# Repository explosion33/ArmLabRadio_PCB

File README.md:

# ArmLabRadio_PCB
KiCad files for CC1200 and STM32 based 2m / 70cm radio

## Software
This is the hardware repo for the project, checkout

[CC1200stm32](https://github.com/explosion33/CC1200stm32) for the embedded device code

[ArmLabCC1200](https://github.com/explosion33/ArmLabCC1200) for Serial / I2C inteface libraries

## Other
checkout

[RGRadioAPI](https://github.com/explosion33/RGRadioApi) for an example use case

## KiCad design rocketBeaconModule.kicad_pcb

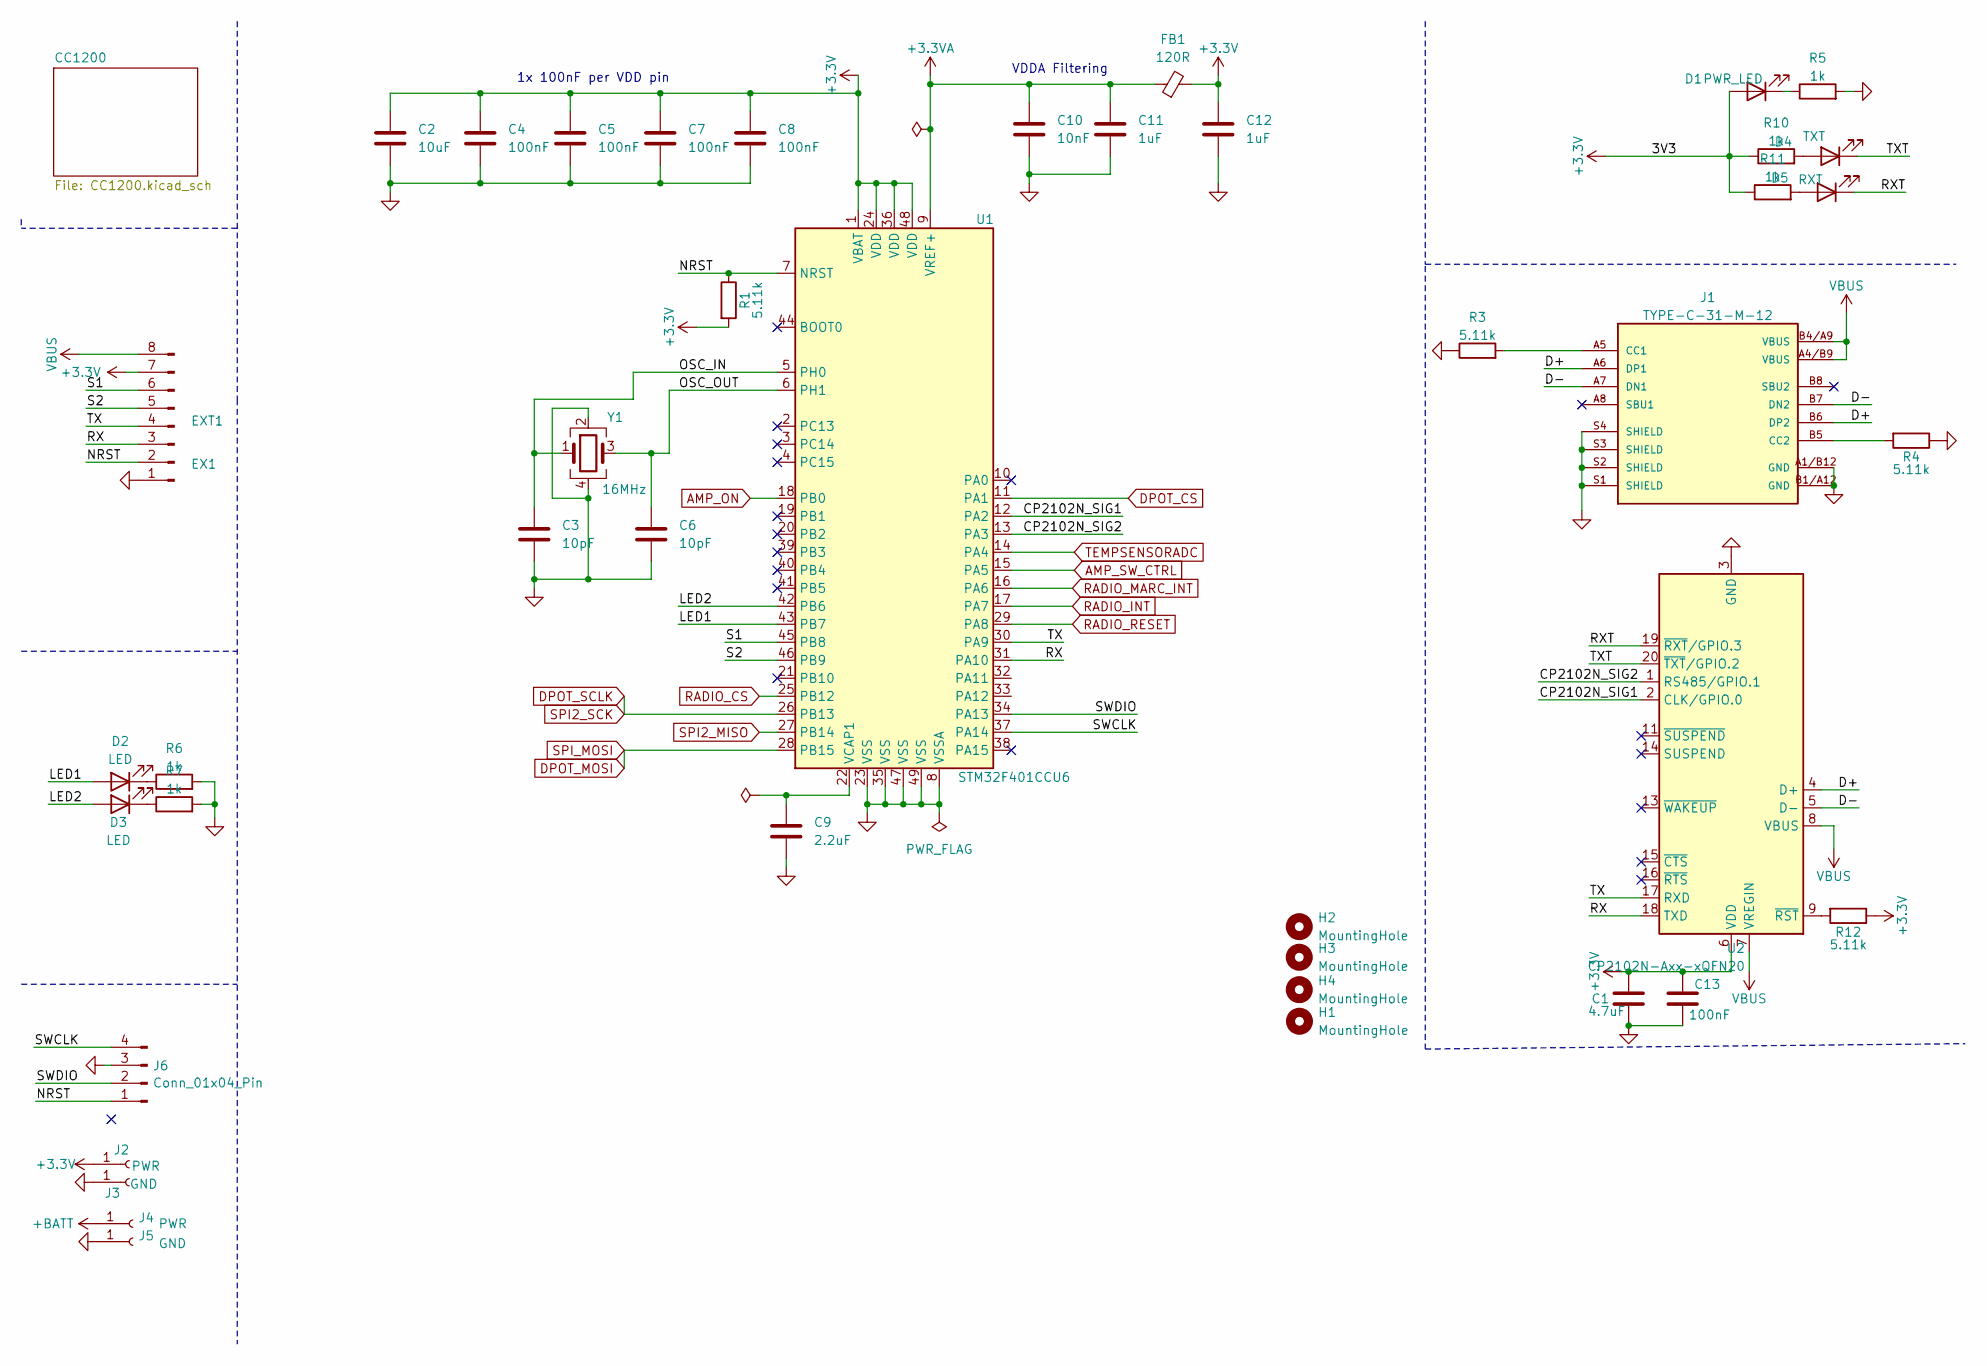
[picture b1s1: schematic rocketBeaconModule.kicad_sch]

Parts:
C1: 4.7uF; C_0603_1608Metric; LCSC Part C71631
C2: 10uF; C_0603_1608Metric; LCSC Part C19702
C3, C6: 10pF; C_0402_1005Metric; LCSC Part C32949
C4, C5, C7, C8, C13: 100nF; C_0402_1005Metric; LCSC Part C307331
C9: 2.2uF; C_0402_1005Metric; LCSC Part C12530
C10: 10nF; C_0402_1005Metric; LCSC Part C15195
C11, C12: 1uF; C_0402_1005Metric; LCSC Part C52923
D1: PWR_LED; LED_0402_1005Metric; LCSC Part C5160717
D2: LED; LED_0402_1005Metric; LCSC Part C131223
D3: LED; LED_0402_1005Metric; LCSC Part C130722
D4: TXT; LED_0402_1005Metric; LCSC Part C136765
D5: RXT; LED_0402_1005Metric; LCSC Part C130722
EX1: EXT1; Molex_200528-0080_1x08-1MP_P1.00mm_Horizontal; LCSC Part C132510
FB1: 120R; L_0603_1608Metric; LCSC Part C85831
H1, H2, H3, H4: MountingHole; MountingHole_2.2mm_M2
J1: TYPE-C-31-M-12; HRO_TYPE-C-31-M-12; PARTREV 2020.12.08; LCSC Part C165948
J2, J4: PWR; TestPoint_THTPad_4.0x4.0mm_Drill2.0mm
J3, J5: GND; TestPoint_THTPad_4.0x4.0mm_Drill2.0mm
J6: Conn_01x04_Pin; PinHeader_1x04_P2.54mm_Vertical
R1, R3, R4, R12: 5.11k; R_0402_1005Metric; LCSC Part C25906
R5, R6, R7, R10, R11: 1k; R_0402_1005Metric; LCSC Part C11702
U1: STM32F401CCU6; QFN-48-1EP_7x7mm_P0.5mm_EP5.6x5.6mm; LCSC Part C79861
U2: CP2102N-Axx-xQFN20; WFQFN-20; LCSC Part C969913
Y1: 16MHz; Crystal_SMD_3225-4Pin_3.2x2.5mm; LCSC Part C13738

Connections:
+3.3V: C1.1, C2.1, C4.1, C5.1, C7.1, C8.1, C12.1, C13.1, D1.2 (A), EX1.7, FB1.2, J2.1, R1.2, R10.1, R11.1, R12.1, U1.1 (VBAT), U1.24 (VDD), U1.36 (VDD), U1.48 (VDD), U2.6 (VDD); also elsewhere on the board
+3.3VA: C10.1, C11.1, FB1.1, U1.9 (VREF+)
+BATT: J4.1; also elsewhere on the board
/CP2102N_SIG1: U1.12 (PA2), U2.2 (CLK/GPIO.0)
/CP2102N_SIG2: U1.13 (PA3), U2.1 (RS485/GPIO.1)
/D+: J1.A6 (DP1), J1.B6 (DP2), U2.4 (D+)
/D-: J1.A7 (DN1), J1.B7 (DN2), U2.5 (D-)
/LED1: D2.2 (A), U1.43 (PB7)
/LED2: D3.2 (A), U1.42 (PB6)
/NRST: EX1.2, J6.1, R1.1, U1.7 (NRST)
/OSC_IN: C3.1, U1.5 (PH0), Y1.1
/OSC_OUT: C6.1, U1.6 (PH1), Y1.3
/RX: EX1.3, U1.31 (PA10), U2.18 (TXD)
/RXT: D5.1 (K), U2.19 (~RXT/GPIO.3)
/S1: EX1.6, U1.45 (PB8)
/S2: EX1.5, U1.46 (PB9)
/SWCLK: J6.4, U1.37 (PA14)
/SWDIO: J6.2, U1.34 (PA13)
/TX: EX1.4, U1.30 (PA9), U2.17 (RXD)
/TXT: D4.1 (K), U2.20 (~TXT/GPIO.2)
AMP_ON: U1.18 (PB0); also elsewhere on the board
AMP_SW_CTRL: U1.15 (PA5); also elsewhere on the board
DPOT_CS: U1.11 (PA1); also elsewhere on the board
DPOT_MOSI: U1.28 (PB15); also elsewhere on the board
DPOT_SCLK: U1.26 (PB13); also elsewhere on the board
GND: C1.2, C2.2, C3.2, C4.2, C5.2, C6.2, C7.2, C8.2, C9.2, C10.2, C11.2, C12.2, C13.2, EX1.1, J1.A1/B12 (GND), J1.B1/A12 (GND), J1.S1 (SHIELD), J1.S2 (SHIELD), J1.S3 (SHIELD), J1.S4 (SHIELD), J3.1, J5.1, J6.3, R3.1, R4.1, R5.2, R6.2, R7.2, U1.8 (VSSA), U1.23 (VSS), U1.35 (VSS), U1.47 (VSS), U1.49 (VSS), U2.3 (GND), U2.12 (GND), Y1.2, Y1.4; also elsewhere on the board
unnamed: D1.1 (K), R5.1
unnamed: D2.1 (K), R6.1
unnamed: D3.1 (K), R7.1
unnamed: D4.2 (A), R10.2
unnamed: D5.2 (A), R11.2
unnamed: J1.A5 (CC1), R3.2
unnamed: J1.B5 (CC2), R4.2
unnamed: C9.1, U1.22 (VCAP1)
unnamed: R12.2, U2.9 (~RST)
RADIO_CS: U1.25 (PB12); also elsewhere on the board
RADIO_INT: U1.17 (PA7); also elsewhere on the board
RADIO_MARC_INT: U1.16 (PA6); also elsewhere on the board
RADIO_RESET: U1.29 (PA8); also elsewhere on the board
SPI2_MISO: U1.27 (PB14); also elsewhere on the board
TEMPSENSORADC: U1.14 (PA4); also elsewhere on the board
VBUS: EX1.8, J1.A4/B9 (VBUS), J1.B4/A9 (VBUS), U2.7 (VREGIN), U2.8 (VBUS)

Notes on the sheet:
VDDA Filtering
1x 100nF per VDD pin

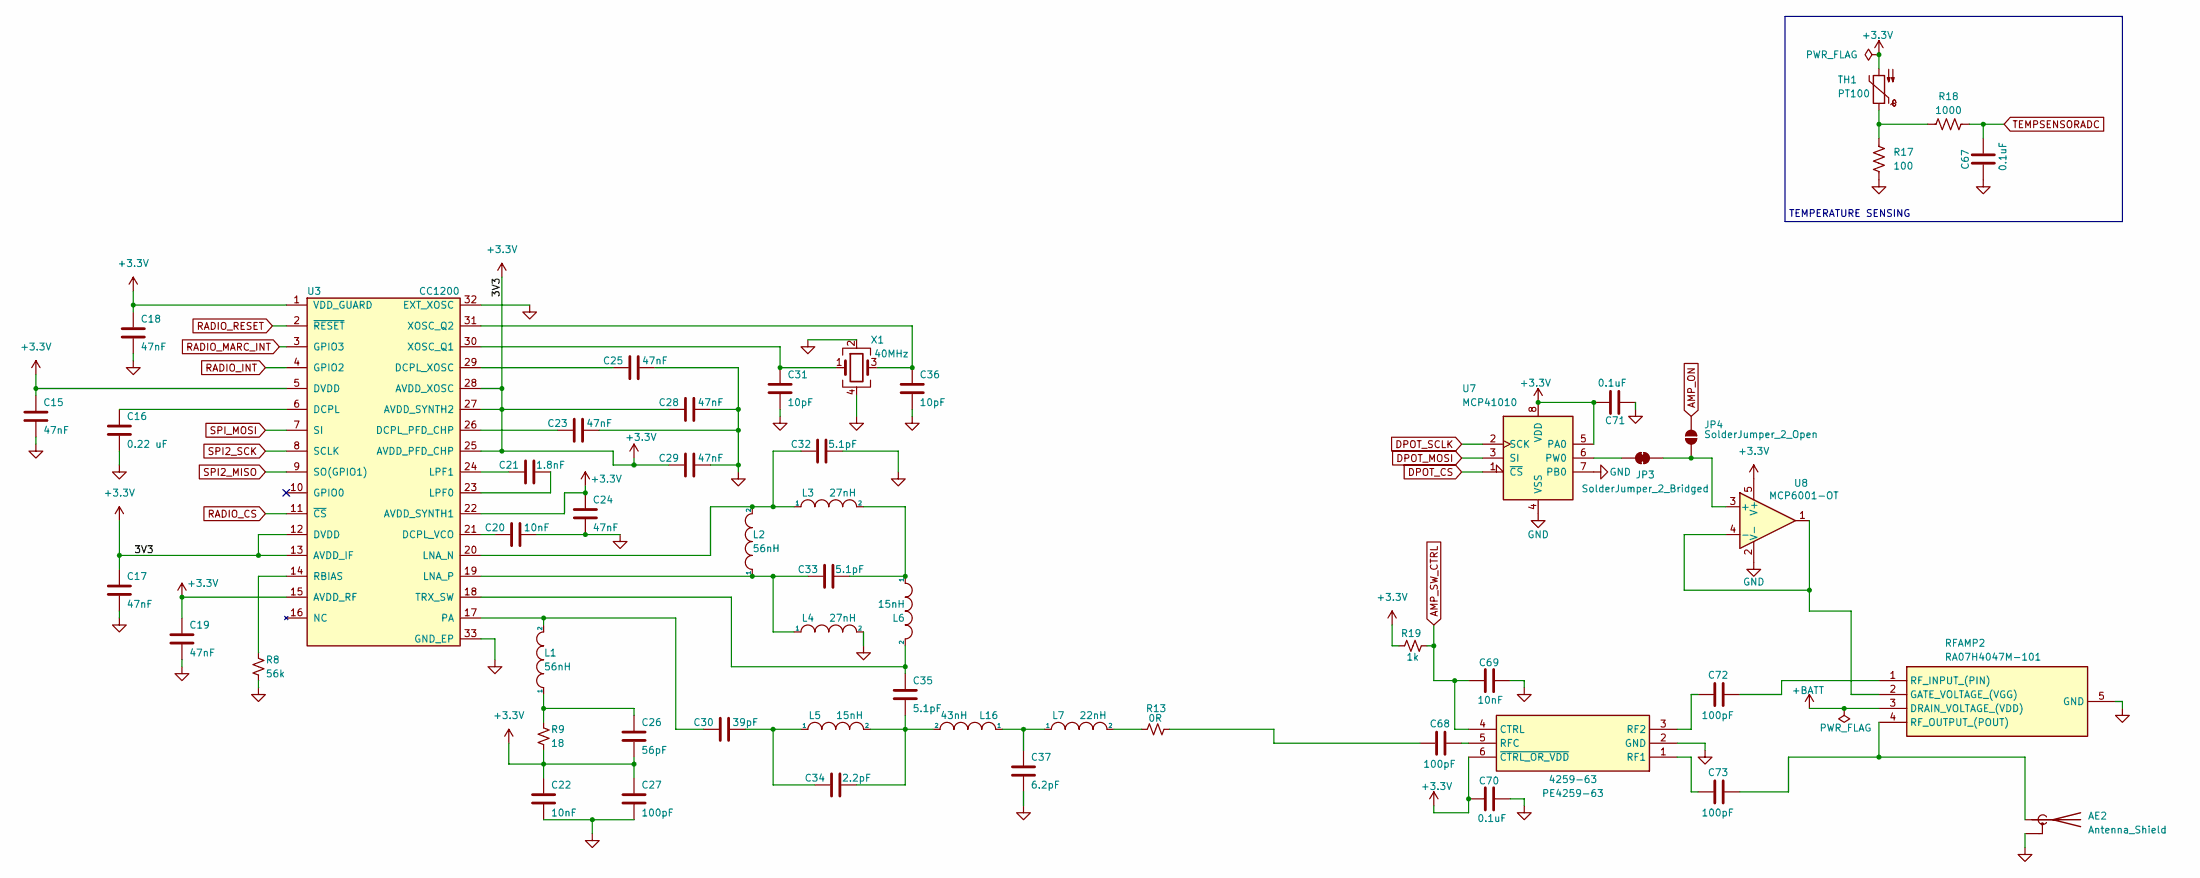
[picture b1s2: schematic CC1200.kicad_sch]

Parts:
AE2: Antenna_Shield; SMA_Amphenol_132134-11_Vertical; LCSC Part C496549
C15, C17, C18, C19, C23, C24, C25, C28, C29: 47nF; C_0402_1005Metric; LCSC Part C508865
C16: 0.22 uF; C_0402_1005Metric; LCSC Part C16772
C20, C22: 10nF; C_0402_1005Metric; LCSC Part C15195
C21: 1.8nF; C_0402_1005Metric; LCSC Part C162192
C26: 56pF; C_0402_1005Metric; LCSC Part C335543
C27: 100pF; C_0402_1005Metric; LCSC Part C126492
C30: 39pF; C_0402_1005Metric; LCSC Part C86288
C31, C36: 10pF; C_0402_1005Metric; LCSC Part C32949
C32, C33, C35: 5.1pF; C_0402_1005Metric; LCSC Part C281761
C34: 2.2pF; C_0402_1005Metric; LCSC Part C159806
C37: 6.2pF; C_0402_1005Metric; LCSC Part C325456
C67, C71: 0.1uF; C_0402_1005Metric; LCSC Part C1525
C68, C72, C73: 100pF; C_0402_1005Metric; LCSC C1546
C69: 10nF; C_0402_1005Metric; LCSC C15195
C70: 0.1uF; C_0402_1005Metric; LCSC C1525
JP3: SolderJumper_2_Bridged; SolderJumper-2_P1.3mm_Bridged_RoundedPad1.0x1.5mm
JP4: SolderJumper_2_Open; SolderJumper-2_P1.3mm_Open_RoundedPad1.0x1.5mm
L1, L2: 56nH; C_0402_1005Metric; LCSC Part C167484
L3, L4: 27nH; C_0402_1005Metric; LCSC Part C12669
L5, L6: 15nH; C_0402_1005Metric; LCSC Part C27143
L7: 22nH; C_0402_1005Metric; LCSC Part C12670
L16: 43nH; L_0402_1005Metric; LCSC Part C167478
PE4259-63: 4259-63; SOT-363_SC-70-6; Manufacturer_Part_Number 4259-63; LCSC Part C470892
R8: 56k; C_0402_1005Metric; LCSC Part C25796
R9: 18; R_0402_1005Metric; LCSC Part C25084
R13: 0R; C_0402_1005Metric; LCSC Part C138289
R17: 100; R_0402_1005Metric; LCSC Part C25076
R18: 1000; R_0402_1005Metric; LCSC Part C21190
R19: 1k; R_0402_1005Metric; LCSC C11702
RFAMP2: RA07H4047M-101; RA07h4047M; Manufacturer_Part_Number RA07H4047M-101
TH1: PT100; R_0603_1608Metric; LCSC Part C141518
U3: CC1200; QFN-32-1EP_5x5mm_P0.5mm_EP3.45x3.45mm; LCSC Part C122881
U7: MCP41010; SOIC127P599X175-8N; LCSC Part C136395
U8: MCP6001-OT; SOT-23-5; LCSC Part C116490
X1: 40MHz; Oscillator_SMD_Abracon_ASE-4Pin_3.2x2.5mm; LCSC Part C9010

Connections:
+3.3V: C15.1, C17.1, C18.1, C19.1, C22.1, C24.1, C26.2, C27.1, C28.2, C29.2, C70.2, C71.1, PE4259-63.6 (~CTRL_OR_VDD), R9.2, R19.2, TH1.2, U3.1 (VDD_GUARD), U3.5 (DVDD), U3.12 (DVDD), U3.13 (AVDD_IF), U3.15 (AVDD_RF), U3.22 (AVDD_SYNTH1), U3.25 (AVDD_PFD_CHP), U3.27 (AVDD_SYNTH2), U3.28 (AVDD_XOSC), U7.5 (PA0), U7.8 (VDD), U8.5 (V+); also elsewhere on the board
+BATT: RFAMP2.3 (DRAIN_VOLTAGE_(VDD)); also elsewhere on the board
AMP_ON: JP4.2 (B); also elsewhere on the board
AMP_SW_CTRL: C69.2, PE4259-63.4 (CTRL), R19.1; also elsewhere on the board
DPOT_CS: U7.1 (~CS); also elsewhere on the board
DPOT_MOSI: U3.7 (SI), U7.3 (SI); also elsewhere on the board
DPOT_SCLK: U3.8 (SCLK), U7.2 (SCK); also elsewhere on the board
GND: AE2.2 (Shield), C15.2, C16.2, C17.2, C18.2, C19.2, C20.1, C22.2, C23.1, C24.2, C25.1, C27.2, C28.1, C29.1, C31.2, C32.1, C36.2, C37.2, C67.2, C69.1, C70.1, C71.2, L4.2, PE4259-63.2 (GND), R8.2, R17.2, RFAMP2.5 (GND), U3.32 (EXT_XOSC), U3.33 (GND_EP), U7.4 (VSS), U7.7 (PB0), U8.2 (V-), X1.2, X1.4; also elsewhere on the board
unnamed: AE2.1 (A), C73.2, RFAMP2.4 (RF_OUTPUT_(POUT))
unnamed: C26.1, L1.1, R9.1
unnamed: C30.1, C34.2, L5.1
unnamed: C33.1, L3.2, L6.1
unnamed: C34.1, C35.2, L5.2, L16.2
unnamed: C37.1, L7.1, L16.1
unnamed: C68.1, R13.2
unnamed: JP3.1 (A), U7.6 (PW0)
unnamed: JP3.2 (B), JP4.1 (A), U8.3 (+)
unnamed: L7.2, R13.1
unnamed: C73.1, PE4259-63.1 (RF1)
unnamed: C72.1, PE4259-63.3 (RF2)
unnamed: C68.2, PE4259-63.5 (RFC)
unnamed: R17.1, R18.1, TH1.1
unnamed: RFAMP2.2 (GATE_VOLTAGE_(VGG)), U8.1, U8.4 (-)
unnamed: C72.2, RFAMP2.1 (RF_INPUT_(PIN))
unnamed: C16.1, U3.6 (DCPL)
unnamed: C23.2, U3.26 (DCPL_PFD_CHP)
unnamed: C20.2, U3.21 (DCPL_VCO)
unnamed: C25.2, U3.29 (DCPL_XOSC)
unnamed: C32.2, L2.2, L3.1, U3.20 (LNA_N)
unnamed: C33.2, L2.1, L4.1, U3.19 (LNA_P)
unnamed: C21.1, U3.23 (LPF0)
unnamed: C21.2, U3.24 (LPF1)
unnamed: C30.2, L1.2, U3.17 (PA)
unnamed: R8.1, U3.14 (RBIAS)
unnamed: C35.1, L6.2, U3.18 (TRX_SW)
unnamed: C31.1, U3.30 (XOSC_Q1), X1.1
unnamed: C36.1, U3.31 (XOSC_Q2), X1.3
RADIO_CS: U3.11 (~CS); also elsewhere on the board
RADIO_INT: U3.4 (GPIO2); also elsewhere on the board
RADIO_MARC_INT: U3.3 (GPIO3); also elsewhere on the board
RADIO_RESET: U3.2 (~RESET); also elsewhere on the board
SPI2_MISO: U3.9 (SO(GPIO1)); also elsewhere on the board
TEMPSENSORADC: C67.1, R18.2; also elsewhere on the board

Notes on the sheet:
TEMPERATURE SENSING

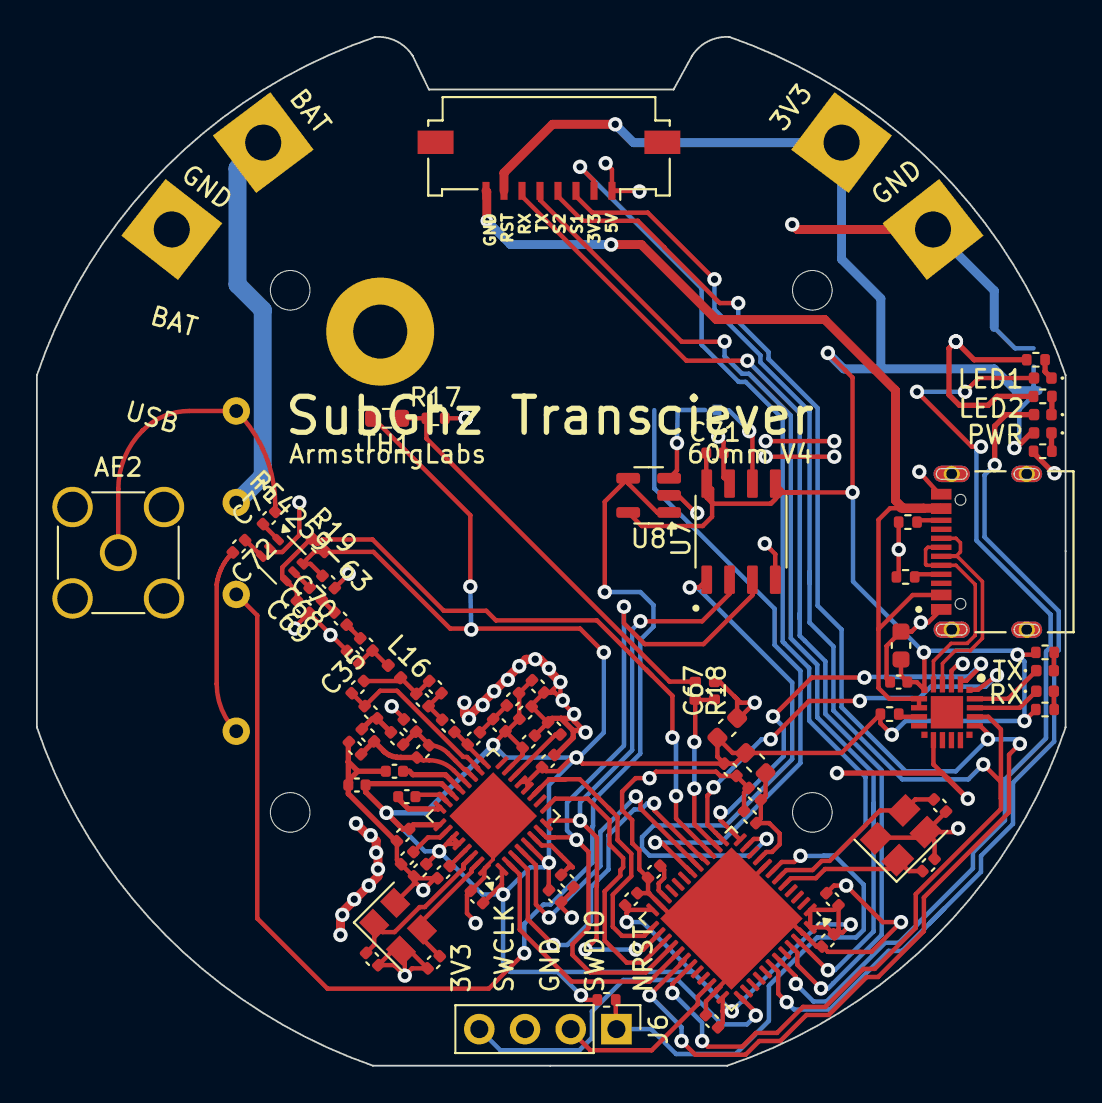
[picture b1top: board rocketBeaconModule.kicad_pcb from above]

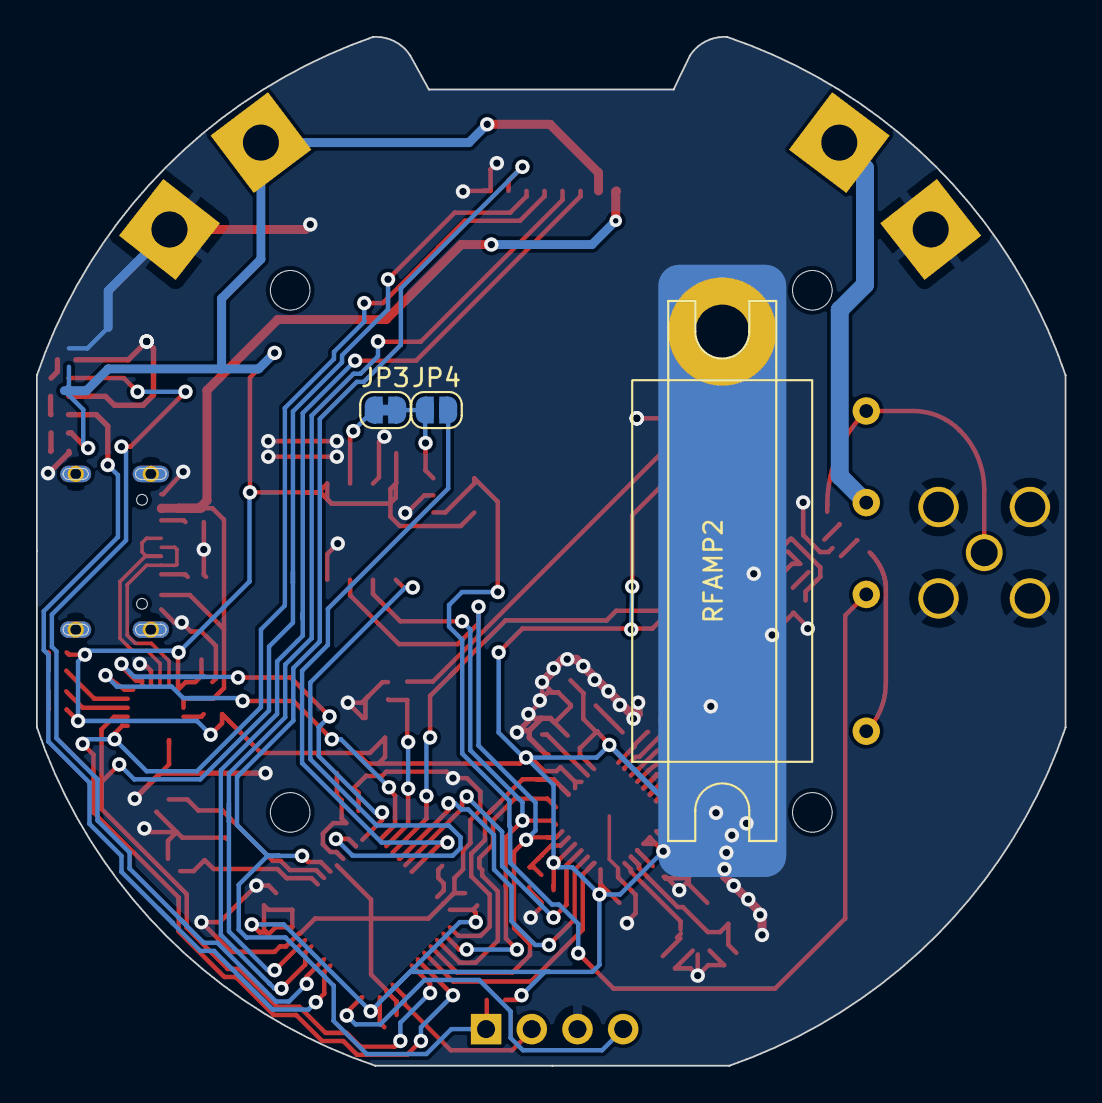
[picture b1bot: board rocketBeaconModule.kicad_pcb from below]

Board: 2 copper layers, 57.2 x 57.2 mm, 96 parts (5 on the bottom side), 71 nets.

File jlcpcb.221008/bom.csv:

Designator,Footprint,Quantity,Value,LCSC Part #
J3,HRO_TYPE-C-31-M-12,1,TYPE-C-31-M-12,
C4,C_0402_1005Metric,1,100n,
SWD1,PinHeader_1x04_P2.54mm_Vertical,1,FLASH,
C10,C_0402_1005Metric,1,10n,
C18,C_0402_1005Metric,1,47nF,
C7,C_0402_1005Metric,1,100n,
P1,SMA_Amphenol_132134-11_Vertical,1,AntMount,
R3,R_0402_1005Metric,1,1k,
D1,LED_0603_1608Metric,1,LED,
C26,C_0402_1005Metric,1,56pF,
C29,C_0402_1005Metric,1,47nF,
C32,C_0402_1005Metric,1,5.1pF,
C22,C_0402_1005Metric,1,10nF,
C6,C_0402_1005Metric,1,10p,
C21,C_0402_1005Metric,1,1.8nF,
R8,R_0402_1005Metric,1,5.11k,
J1,PinSocket_1x07_P2.54mm_Vertical,1,Main Bus,
L5,C_0402_1005Metric,1,15nH,
FB1,L_0603_1608Metric,1,120R,
C19,C_0402_1005Metric,1,47nF,
C12,C_0402_1005Metric,1,1u,
C23,C_0402_1005Metric,1,47nF,
R4,R_0402_1005Metric,1,1k,
U1,QFN-48-1EP_7x7mm_P0.5mm_EP5.6x5.6mm,1,STM32F401CCU6,
L7,C_0402_1005Metric,1,43nH,
C9,C_0402_1005Metric,1,2.2u,
C15,C_0402_1005Metric,1,47nF,
J2,PinSocket_1x04_P2.54mm_Vertical,1,Jumper Select,
C24,C_0402_1005Metric,1,47nF,
L2,C_0402_1005Metric,1,56nH,
U3,QFN-32-1EP_5x5mm_P0.5mm_EP3.45x3.45mm,1,CC1200,
H4,MountingHole_3.2mm_M3,1,MountingHole,
L6,C_0402_1005Metric,1,15nH,
C25,C_0402_1005Metric,1,47nF,
R9,R_0402_1005Metric,1,5.11k,
C11,C_0402_1005Metric,1,1u,
C31,C_0402_1005Metric,1,10pF,
C34,C_0402_1005Metric,1,2.2pF,
C36,C_0402_1005Metric,1,10pF,
C28,C_0402_1005Metric,1,47nF,
C8,C_0402_1005Metric,1,100n,
X1,Oscillator_SMD_Abracon_ASE-4Pin_3.2x2.5mm,1,40mhz,
D2,LED_0603_1608Metric,1,LED,
C17,C_0402_1005Metric,1,47nF,
C1,C_0402_1005Metric,1,100n,
C16,C_0402_1005Metric,1,0.22 uF,
R6,C_0402_1005Metric,1,18,
C14,C_0805_2012Metric,1,22u,
C5,C_0402_1005Metric,1,100n,
C33,C_0402_1005Metric,1,5.1pF,
Y1,Crystal_SMD_3225-4Pin_3.2x2.5mm,1,16MHz,
L3,C_0402_1005Metric,1,27nH,
C37,C_0402_1005Metric,1,6.2pF,
H2,MountingHole_3.2mm_M3,1,MountingHole,
L4,C_0402_1005Metric,1,27nH,
R1,R_0402_1005Metric,1,1.5k,
R7,R_0402_1005Metric,1,1k,
R2,R_0402_1005Metric,1,1.5k,
C30,C_0402_1005Metric,1,39pF,
H3,MountingHole_3.2mm_M3,1,MountingHole,
C3,C_0402_1005Metric,1,10p,
C35,C_0402_1005Metric,1,5.1pF,
L8,C_0402_1005Metric,1,22nH,
C20,C_0402_1005Metric,1,10nF,
C2,C_0603_1608Metric,1,10u,
U2,SOT-223-3_TabPin2,1,AMS1117-3.3,
R5,C_0402_1005Metric,1,56k,
C13,C_0805_2012Metric,1,22u,
H1,MountingHole_3.2mm_M3,1,MountingHole,
D3,LED_0603_1608Metric,1,LED,
L1,C_0402_1005Metric,1,56nH,
C27,C_0402_1005Metric,1,100pF,

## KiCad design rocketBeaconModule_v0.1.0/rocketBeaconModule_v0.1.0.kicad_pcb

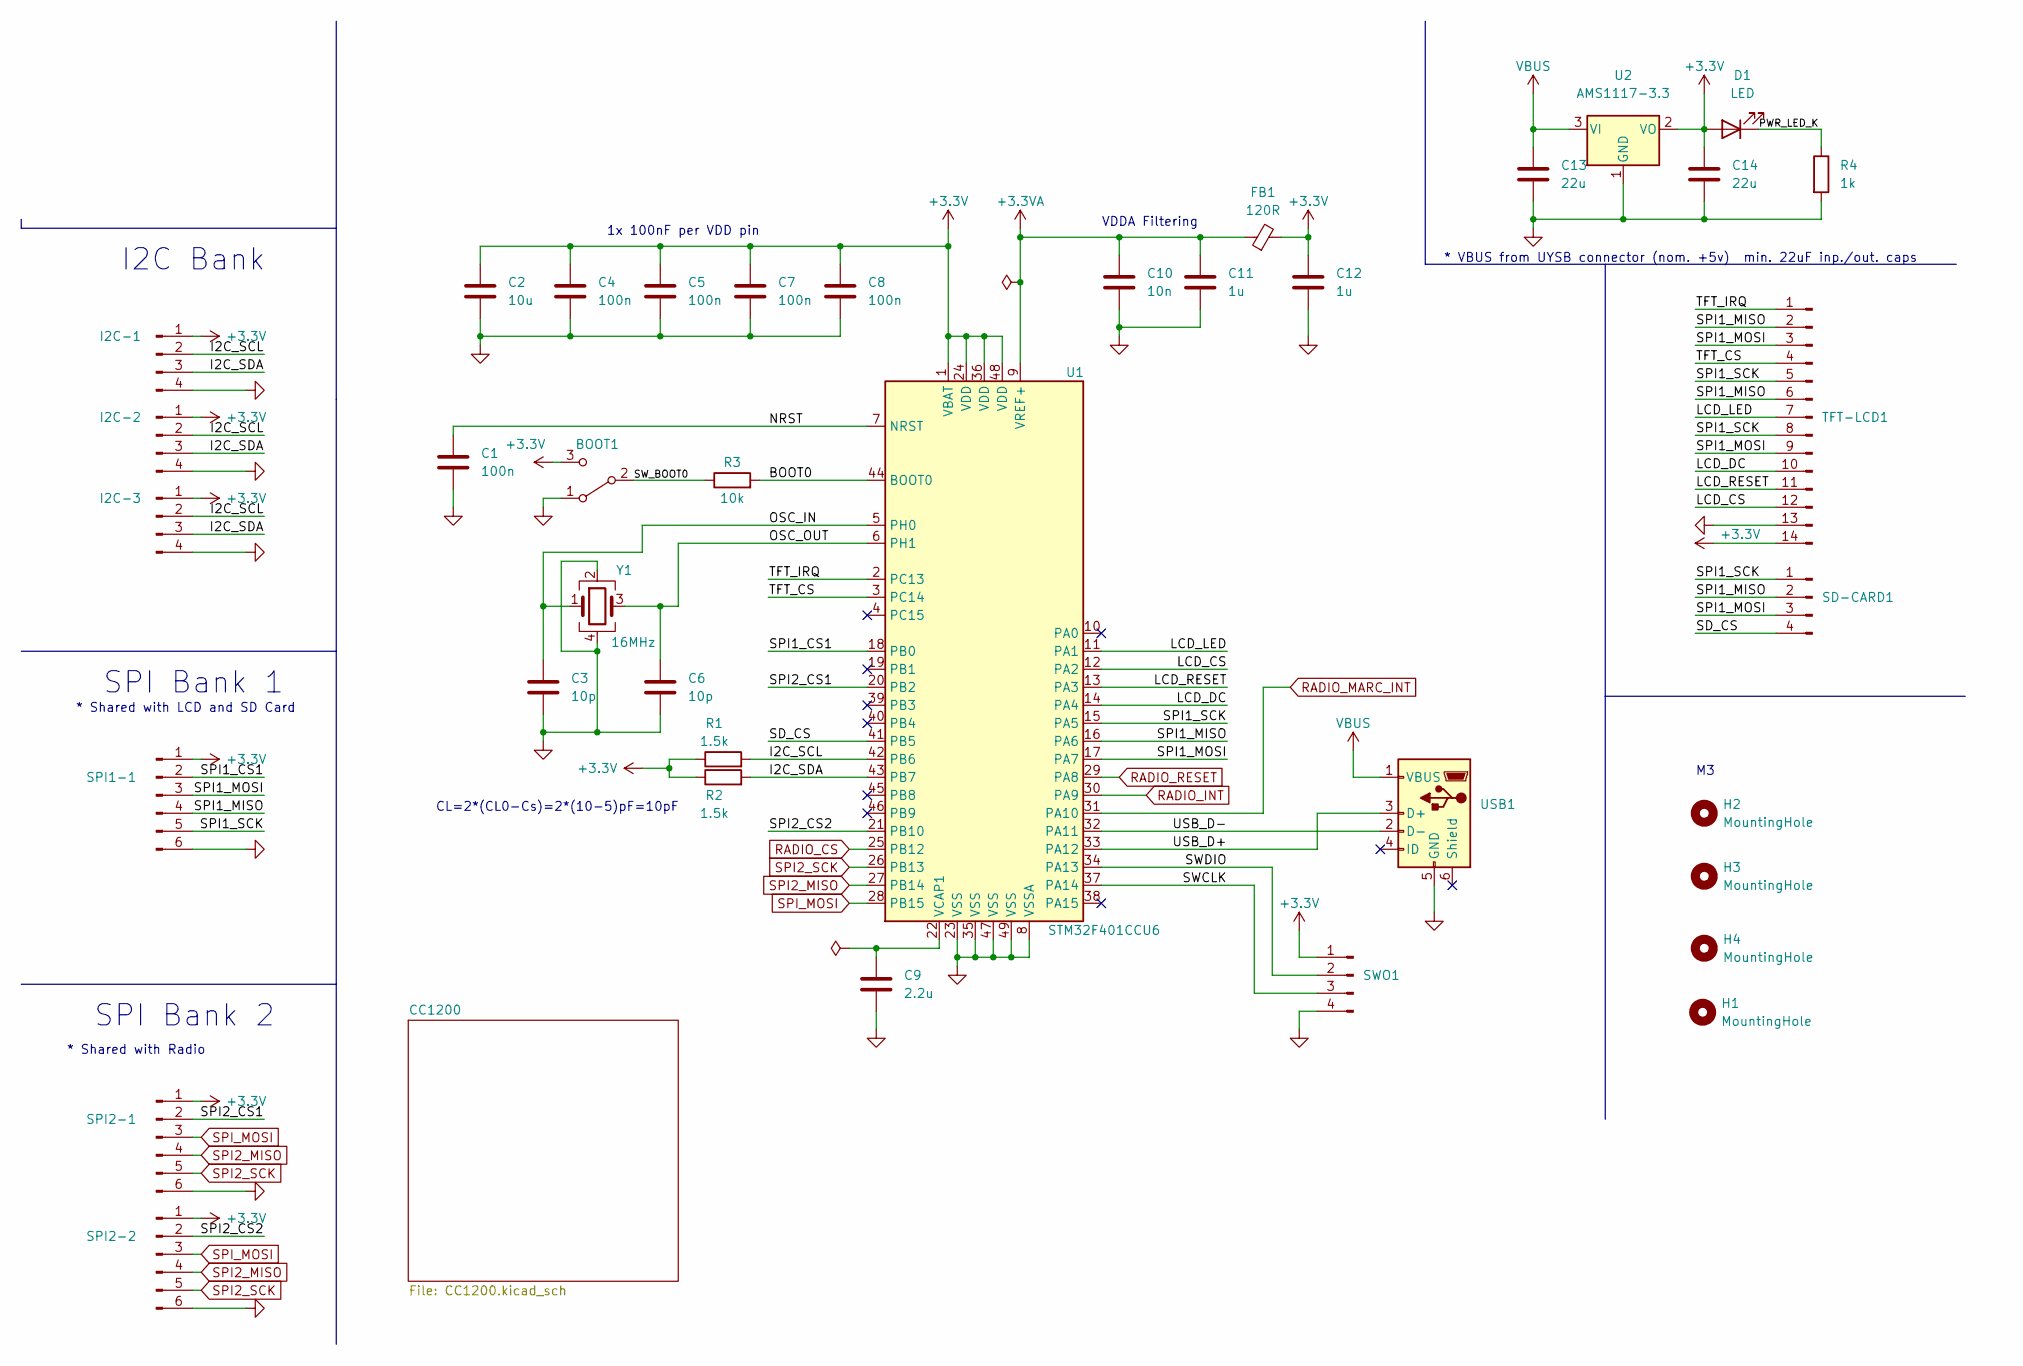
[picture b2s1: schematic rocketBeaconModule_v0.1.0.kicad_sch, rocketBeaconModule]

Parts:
BOOT1: SW_SPDT; SW_SPDT_PCM12
C1, C4, C5, C7, C8: 100n; C_0402_1005Metric
C2: 10u; C_0603_1608Metric
C3, C6: 10p; C_0402_1005Metric
C9: 2.2u; C_0402_1005Metric
C10: 10n; C_0402_1005Metric
C11, C12: 1u; C_0402_1005Metric
C13, C14: 22u; C_0805_2012Metric
D1: LED; LED_0603_1608Metric
FB1: 120R; L_0603_1608Metric
H1, H2, H3, H4: MountingHole; MountingHole_3.2mm_M3
I2C-1: I2C - 1; PinHeader_1x04_P2.54mm_Horizontal
I2C-2: I2C - 2; PinHeader_1x04_P2.54mm_Horizontal
I2C-3: I2C - 3; PinHeader_1x04_P2.54mm_Horizontal
R1, R2: 1.5k; R_0402_1005Metric
R3: 10k; R_0402_1005Metric
R4: 1k; R_0402_1005Metric
SD-CARD1: SD Card; PinSocket_1x04_P2.54mm_Vertical
SPI1-1: SPI1 - 1; PinHeader_1x06_P2.54mm_Horizontal
SPI2-1: SPI2 - 1; PinHeader_1x06_P2.54mm_Horizontal
SPI2-2: SPI2 - 2; PinHeader_1x06_P2.54mm_Horizontal
SWO1: SWO; PinHeader_1x04_P2.54mm_Horizontal
TFT-LCD1: TFT LCD; PinSocket_1x14_P2.54mm_Vertical
U1: STM32F401CCU6; QFN-48-1EP_7x7mm_P0.5mm_EP5.6x5.6mm
U2: AMS1117-3.3; SOT-223-3_TabPin2
USB1: USB_B_Micro; USB_Micro-B_Molex_47346-0001
Y1: 16MHz; Crystal_SMD_3225-4Pin_3.2x2.5mm

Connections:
+3.3V: BOOT1.3 (C), C2.1, C4.1, C5.1, C7.1, C8.1, C12.1, C14.1, D1.2 (A), FB1.2, I2C-1.1, I2C-2.1, I2C-3.1, R1.1, R2.1, SPI1-1.1, SPI2-1.1, SPI2-2.1, SWO1.1, TFT-LCD1.14, U1.1 (VBAT), U1.24 (VDD), U1.36 (VDD), U1.48 (VDD), U2.2 (VO); also elsewhere on the board
+3.3VA: C10.1, C11.1, FB1.1, U1.9 (VREF+)
/BOOT0: R3.2, U1.44 (BOOT0)
/I2C_SCL: I2C-1.2, I2C-2.2, I2C-3.2, R1.2, U1.42 (PB6)
/I2C_SDA: I2C-1.3, I2C-2.3, I2C-3.3, R2.2, U1.43 (PB7)
/LCD_CS: TFT-LCD1.12, U1.12 (PA2)
/LCD_DC: TFT-LCD1.10, U1.14 (PA4)
/LCD_LED: TFT-LCD1.7, U1.11 (PA1)
/LCD_RESET: TFT-LCD1.11, U1.13 (PA3)
/NRST: C1.1, U1.7 (NRST)
/OSC_IN: C3.1, U1.5 (PH0), Y1.1
/OSC_OUT: C6.1, U1.6 (PH1), Y1.3
/PWR_LED_K: D1.1 (K), R4.1
/SD_CS: SD-CARD1.4, U1.41 (PB5)
/SPI1_CS1: SPI1-1.2, U1.18 (PB0)
/SPI1_MISO: SD-CARD1.2, SPI1-1.4, TFT-LCD1.2, TFT-LCD1.6, U1.16 (PA6)
/SPI1_MOSI: SD-CARD1.3, SPI1-1.3, TFT-LCD1.3, TFT-LCD1.9, U1.17 (PA7)
/SPI1_SCK: SD-CARD1.1, SPI1-1.5, TFT-LCD1.5, TFT-LCD1.8, U1.15 (PA5)
/SPI2_CS1: SPI2-1.2, U1.20 (PB2)
/SPI2_CS2: SPI2-2.2, U1.21 (PB10)
/SWCLK: SWO1.3, U1.37 (PA14); also elsewhere on the board
/SWDIO: SWO1.2, U1.34 (PA13); also elsewhere on the board
/SW_BOOT0: BOOT1.2 (B), R3.1; also elsewhere on the board
/TFT_CS: TFT-LCD1.4, U1.3 (PC14)
/TFT_IRQ: TFT-LCD1.1, U1.2 (PC13)
/USB_D+: U1.33 (PA12), USB1.3 (D+); also elsewhere on the board
/USB_D-: U1.32 (PA11), USB1.2 (D-); also elsewhere on the board
GND: BOOT1.1 (A), C1.2, C2.2, C3.2, C4.2, C5.2, C6.2, C7.2, C8.2, C9.2, C10.2, C11.2, C12.2, C13.2, C14.2, I2C-1.4, I2C-2.4, I2C-3.4, R4.2, SPI1-1.6, SPI2-1.6, SPI2-2.6, SWO1.4, TFT-LCD1.13, U1.8 (VSSA), U1.23 (VSS), U1.35 (VSS), U1.47 (VSS), U1.49 (VSS), U2.1 (GND), USB1.5 (GND), Y1.2, Y1.4; also elsewhere on the board
unnamed: C9.1, U1.22 (VCAP1)
RADIO_CS: U1.25 (PB12); also elsewhere on the board
RADIO_INT: U1.30 (PA9); also elsewhere on the board
RADIO_MARC_INT: U1.31 (PA10); also elsewhere on the board
RADIO_RESET: U1.29 (PA8); also elsewhere on the board
SPI2_MISO: SPI2-1.4, SPI2-2.4, U1.27 (PB14); also elsewhere on the board
SPI2_SCK: SPI2-1.5, SPI2-2.5, U1.26 (PB13); also elsewhere on the board
SPI_MOSI: SPI2-1.3, SPI2-2.3, U1.28 (PB15); also elsewhere on the board
VBUS: C13.1, U2.3 (VI), USB1.1 (VBUS); also elsewhere on the board

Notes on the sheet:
SPI Bank 2
VDDA Filtering
* Shared with Radio
1x 100nF per VDD pin
CL=2*(CL0-Cs)=2*(10-5)pF=10pF
SPI Bank 1
* Shared with LCD and SD Card
* VBUS from UYSB connector (nom. +5v) min. 22uF inp./out. caps
I2C Bank

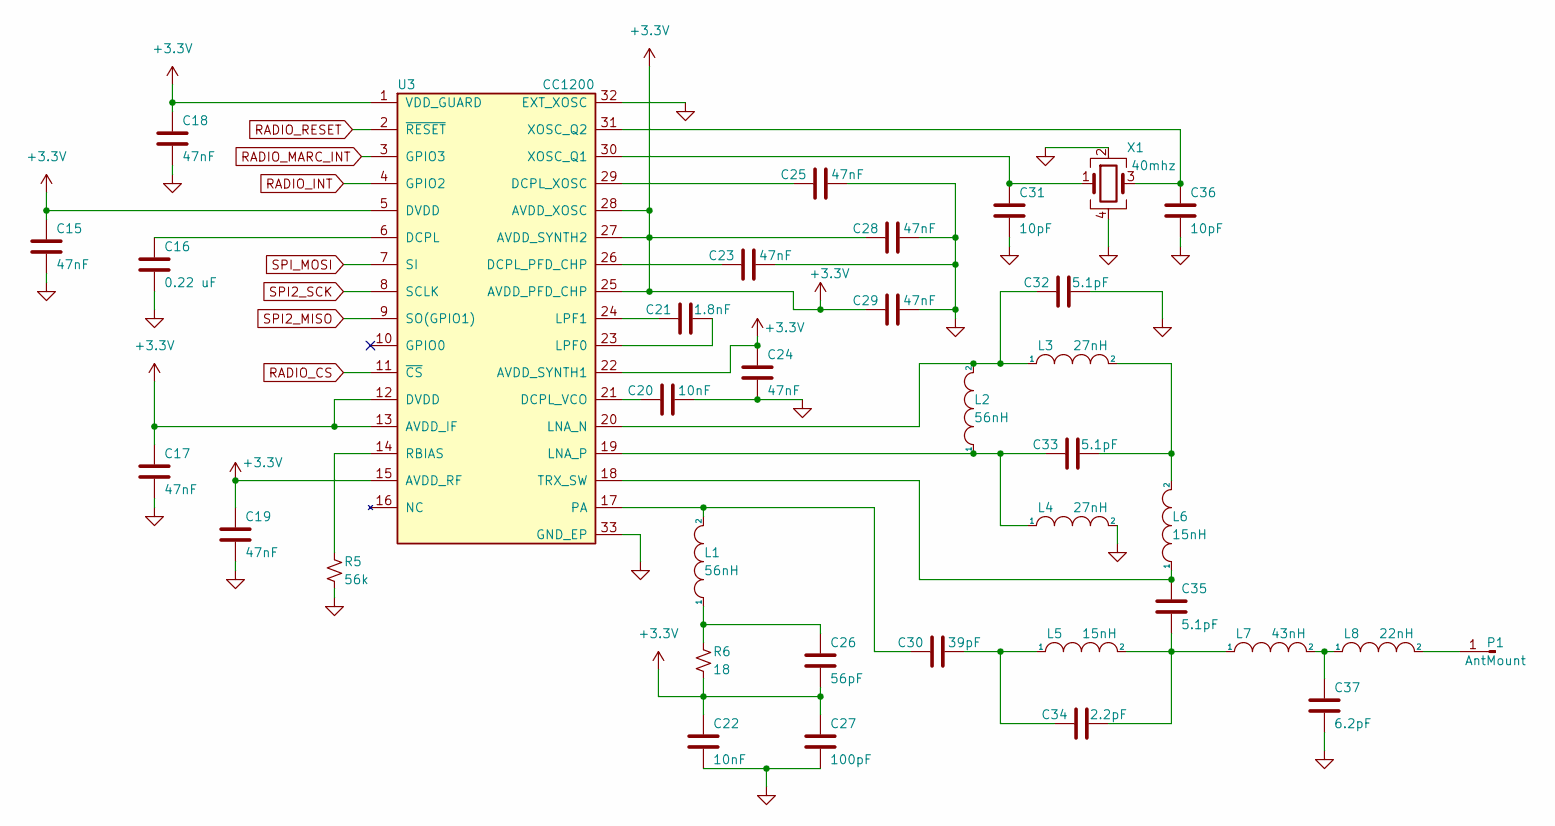
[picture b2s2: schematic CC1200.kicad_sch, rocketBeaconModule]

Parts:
C15, C17, C18, C19, C23, C24, C25, C28, C29: 47nF; C_0402_1005Metric
C16: 0.22 uF; C_0402_1005Metric
C20, C22: 10nF; C_0402_1005Metric
C21: 1.8nF; C_0402_1005Metric
C26: 56pF; C_0402_1005Metric
C27: 100pF; C_0402_1005Metric
C30: 39pF; C_0402_1005Metric
C31, C36: 10pF; C_0402_1005Metric
C32, C33, C35: 5.1pF; C_0402_1005Metric
C34: 2.2pF; C_0402_1005Metric
C37: 6.2pF; C_0402_1005Metric
L1, L2: 56nH; C_0402_1005Metric
L3, L4: 27nH; C_0402_1005Metric
L5, L6: 15nH; C_0402_1005Metric
L7: 43nH; C_0402_1005Metric
L8: 22nH; C_0402_1005Metric
P1: AntMount; SMA_Amphenol_132134-11_Vertical
R5: 56k; C_0402_1005Metric
R6: 18; C_0402_1005Metric
U3: CC1200; QFN-32-1EP_5x5mm_P0.5mm_EP3.45x3.45mm
X1: 40mhz; Oscillator_SMD_Abracon_ASE-4Pin_3.2x2.5mm

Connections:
+3.3V: C15.1, C17.1, C18.1, C19.1, C22.1, C24.1, C26.2, C27.1, C28.2, C29.2, R6.2, U3.1 (VDD_GUARD), U3.5 (DVDD), U3.12 (DVDD), U3.13 (AVDD_IF), U3.15 (AVDD_RF), U3.22 (AVDD_SYNTH1), U3.25 (AVDD_PFD_CHP), U3.27 (AVDD_SYNTH2), U3.28 (AVDD_XOSC); also elsewhere on the board
GND: C15.2, C16.2, C17.2, C18.2, C19.2, C20.1, C22.2, C23.1, C24.2, C25.1, C27.2, C28.1, C29.1, C31.2, C32.1, C36.2, C37.2, L4.2, R5.2, U3.32 (EXT_XOSC), U3.33 (GND_EP), X1.2, X1.4; also elsewhere on the board
unnamed: C16.1, U3.6 (DCPL)
unnamed: C20.2, U3.21 (DCPL_VCO)
unnamed: C21.1, U3.23 (LPF0)
unnamed: C21.2, U3.24 (LPF1)
unnamed: C23.2, U3.26 (DCPL_PFD_CHP)
unnamed: C25.2, U3.29 (DCPL_XOSC)
unnamed: C26.1, L1.1, R6.1
unnamed: C30.1, C34.2, L5.1
unnamed: C30.2, L1.2, U3.17 (PA)
unnamed: C31.1, U3.30 (XOSC_Q1), X1.1
unnamed: C32.2, L2.2, L3.1, U3.20 (LNA_N)
unnamed: C33.1, L3.2, L6.2
unnamed: C33.2, L2.1, L4.1, U3.19 (LNA_P)
unnamed: C34.1, C35.2, L5.2, L7.1
unnamed: C35.1, L6.1, U3.18 (TRX_SW)
unnamed: C36.1, U3.31 (XOSC_Q2), X1.3
unnamed: C37.1, L7.2, L8.1
unnamed: L8.2, P1.1
unnamed: R5.1, U3.14 (RBIAS)
RADIO_CS: U3.11 (~CS); also elsewhere on the board
RADIO_INT: U3.4 (GPIO2); also elsewhere on the board
RADIO_MARC_INT: U3.3 (GPIO3); also elsewhere on the board
RADIO_RESET: U3.2 (~RESET); also elsewhere on the board
SPI2_MISO: U3.9 (SO(GPIO1)); also elsewhere on the board
SPI2_SCK: U3.8 (SCLK); also elsewhere on the board
SPI_MOSI: U3.7 (SI); also elsewhere on the board
